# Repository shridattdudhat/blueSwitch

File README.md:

# ESP32-BLE-Relay-Control
ESP32-BLE-Relay-Control

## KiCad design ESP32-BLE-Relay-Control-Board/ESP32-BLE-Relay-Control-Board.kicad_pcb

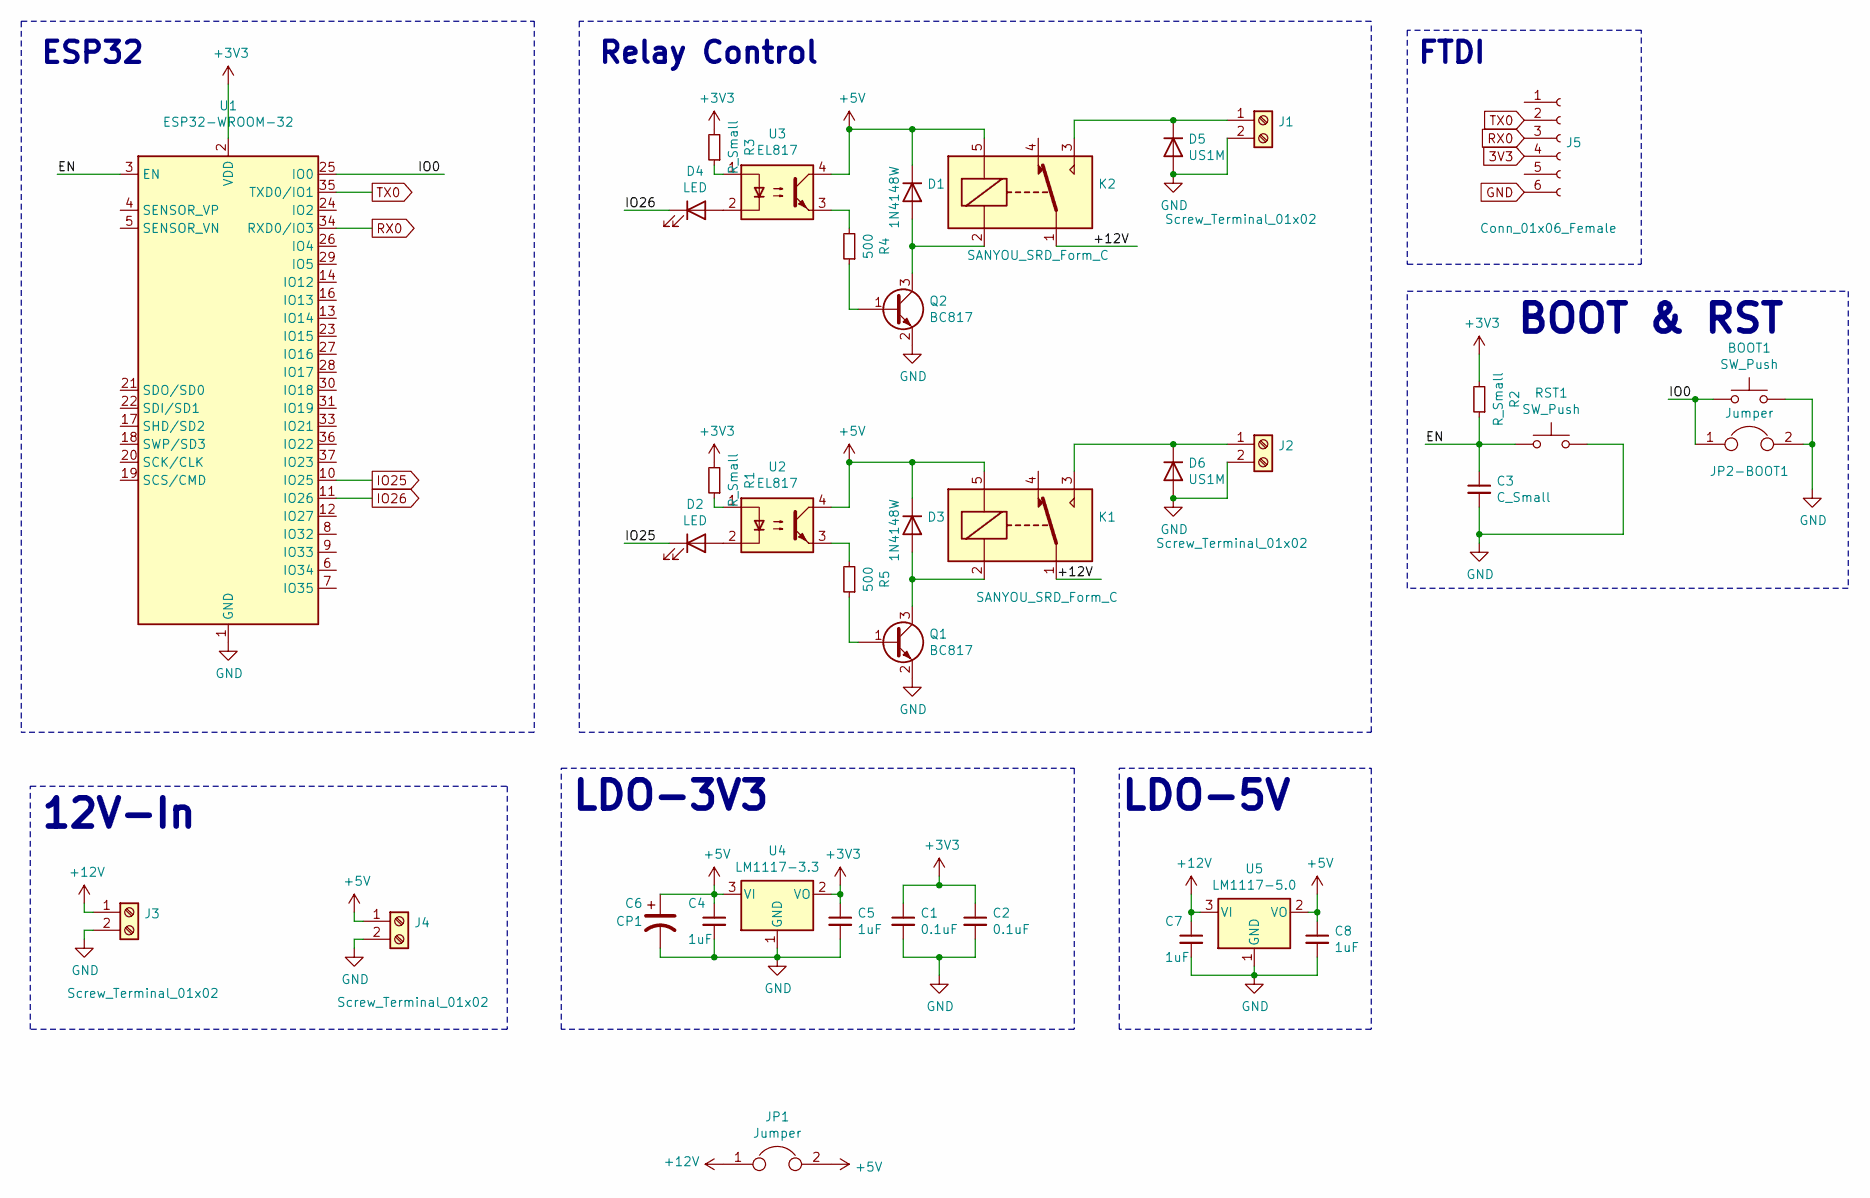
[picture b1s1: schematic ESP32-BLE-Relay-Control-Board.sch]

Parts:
BOOT1: SW_Push; SW_PUSH_6mm
C1, C2: 0.1uF; C_0805_2012Metric_Pad1.15x1.40mm_HandSolder
C3: C_Small; C_0805_2012Metric_Pad1.15x1.40mm_HandSolder
C4, C5, C7, C8: 1uF; C_0805_2012Metric_Pad1.15x1.40mm_HandSolder
C6: CP1; CP_Radial_D12.5mm_P7.50mm
D1, D3: 1N4148W; D_SOD-123
D2, D4: LED; LED_0805_2012Metric
D5, D6: US1M; D_SMA
J1, J2, J3, J4: Screw_Terminal_01x02; TerminalBlock_bornier-2_P5.08mm
J5: Conn_01x06_Female; PinHeader_1x06_P2.54mm_Vertical
JP1, JP2-BOOT1: Jumper; TestPoint_2Pads_Pitch2.54mm_Drill0.8mm
K1, K2: SANYOU_SRD_Form_C; Relay_SPDT_SANYOU_SRD_Series_Form_C
Q1, Q2: BC817; SOT-23
R1, R2, R3: R_Small; R_0603_1608Metric_Pad1.05x0.95mm_HandSolder
R4, R5: 500; R_0603_1608Metric_Pad1.05x0.95mm_HandSolder
RST1: SW_Push; SW_PUSH_6mm
U1: ESP32-WROOM-32
U2, U3: EL817; DIP-4_W7.62mm
U4: LM1117-3.3; SOT-223-3_TabPin2
U5: LM1117-5.0; SOT-223-3_TabPin2

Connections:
3V3: J5.4
+3V3: C1.1, C2.1, C5.1, R1.2, R2.2, R3.2, U1.2 (VDD), U4.2 (VO)
+5V: C4.1, C6.1, C8.1, D1.1 (K), D3.1 (K), J4.1, JP1.2, K1.5, K2.5, U2.4, U3.4, U4.3 (VI), U5.2 (VO)
+12V: C7.1, J3.1, JP1.1, K1.1, K2.1, U5.3 (VI)
/EN: C3.1, R2.1, RST1.1, U1.3 (EN)
/IO0: BOOT1.1, JP2-BOOT1.1, U1.25 (IO0)
GND: BOOT1.2, C1.2, C2.2, C3.2, C4.2, C5.2, C6.2, C7.2, C8.2, D5.2 (A), D6.2 (A), J1.2, J2.2, J3.2, J4.2, J5.6, JP2-BOOT1.2, Q1.2 (E), Q2.2 (E), RST1.2, U1.1 (GND), U1.15 (GND), U1.38 (GND), U1.39 (GND), U4.1 (GND), U5.1 (GND)
IO25: D2.1 (K), U1.10 (IO25)
IO26: D4.1 (K), U1.11 (IO26)
unnamed: D1.2 (A), K2.2, Q2.3 (C)
unnamed: D2.2 (A), U2.2
unnamed: D3.2 (A), K1.2, Q1.3 (C)
unnamed: D4.2 (A), U3.2
unnamed: D5.1 (K), J1.1, K2.3
unnamed: D6.1 (K), J2.1, K1.3
unnamed: Q1.1 (B), R5.1
unnamed: Q2.1 (B), R4.1
unnamed: R1.1, U2.1
unnamed: R3.1, U3.1
unnamed: R4.2, U3.3
unnamed: R5.2, U2.3
RX0: J5.3, U1.34 (RXD0/IO3)
TX0: J5.2, U1.35 (TXD0/IO1)

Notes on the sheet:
ESP32
Relay Control
FTDI
BOOT & RST
LDO-3V3
LDO-5V
12V-In

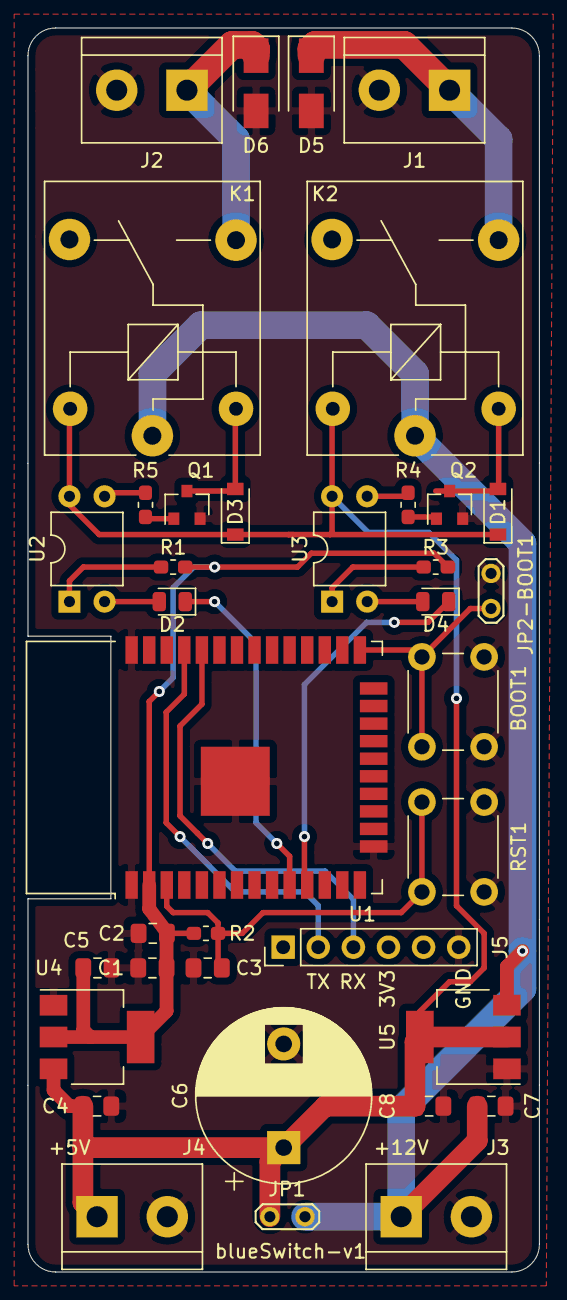
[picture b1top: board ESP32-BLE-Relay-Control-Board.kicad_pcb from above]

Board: 2 copper layers, 37.0 x 90.0 mm, 37 parts (0 on the bottom side), 22 nets.

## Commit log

2020-07-31 Create BLE Project
2020-07-31 BLE RELAY UPDATE
2020-08-03 relay added
2020-08-04 Power in connector added
2020-08-04 5V LDO Added
2020-08-04 gerber generate
2020-08-06 UPDATE, logos added to board
2020-08-06 gerber
